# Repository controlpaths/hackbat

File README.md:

# Hackbat

HackBat is an open-source device designed for hackers and makers to experiment with different pen-testing techniques. The device is based on the Raspberry Pi RP2040 microcontroller and has an RF transceiver, NFC, WIFI, OLED display...

## RP2040

The Raspberry Pi [RP2040](https://www.raspberrypi.com/products/rp2040/specifications/) is the brain of the HackBat. The main features of this MCU are:

- Dual-core Arm Cortex-M0+ processor, flexible clock running up to 133 MHz 264kB on-chip SRAM
- 2 × UART 
- 2 × SPI controllers
- 2 × I2C controllers
- 16 × PWM channels
- 1 × USB 1.1 controller and PHY, with host and device support
- 8 × Programmable I/O (PIO) state machines for custom peripheral support
- Operating temperature -40°C to +85°C
- Drag-and-drop programming using mass storage over USB
- Low-power sleep and dormant modes
- Temperature sensor
- Accelerated integer and floating-point libraries on-chip

The RP2040 can be programmed using Arduino IDE, Python or C++.

## Display

The OLED display used in the HackBat is a 128x64 pixels, with the driver SH110X. The device also allows OLED with SSD1306, but notice that the VCC and GND pins are reversed, so you need to change the 0 ohm resistors of those pins.

## RF

The Hackbat features a [CC1101](https://www.ti.com/product/CC1101) from Texas instruments. CC1101 is a low-cost sub-1 GHz transceiver designed for very low-power wireless applications. The circuit is mainly intended for the ISM (Industrial, scientific and Medical) and SRD (Short Range Device) frequency bands at 315, 433, 868, and 915 MHz, but can easily be programmed for operation at other frequencies in the 300-348 MHz, 387-464 MHz and 779-928 MHz bands

## WIFI

The hackBat features an ESP8266 module, the ESP-12F. This module allow either the HackBat to connect a WIFI network, or generate an access point to allow connections.

The ESP-12F modules can be programmed using the Arduino IDE and the UART conenction. In the HackBat, the ESP-12F is programmed through the RP2040 by using it as USB-UART bridge.

## NFC

HackBat has NFC communication at 13.56MHz. The IC in charge of this peripheral is the [PN532].

PN532 is a highly integrated transceiver module for contactless communication at 13.56 MHz based on the 80C51 microcontroller core supporting different card and reader/writer operating modes.

HackBat uses [this](https://es.aliexpress.com/item/1005006005040320.html?spm=a2g0o.productlist.main.13.65b05927VOBhfq&algo_pvid=9ccfed98-181b-4e28-b2be-488f5ec17187&algo_exp_id=9ccfed98-181b-4e28-b2be-488f5ec17187-6&pdp_npi=4%40dis%21EUR%218.71%210.99%21%21%2166.15%217.50%21%402103854017142998536557342eb34a%2112000035367480068%21sea%21ES%210%21AB&curPageLogUid=pD9zsZTxZuDe&utparam-url=scene%3Asearch%7Cquery_from%3A) integrated module with the PN532.

The communication with the RP2040 is I2C.

## Keyboard emulation

Since the RP2040 has USB host/Device, the HackBat can be used as a keyboard emulator using the Arduinoi `keyboard.h` library.

## Get Yours

The HackBat is open-source, so you can use the output files to manufacture your own in [JLCPCB](https://jlcpcb.com/?from=controlpath). You just need to compress the `output_files` directory, and upload it to [JLCPCB](https://jlcpcb.com/?from=controlpath). 

Remember to change the Surface Finish to **LeadFree HASL** to make your board ROHS compliant.

Then you have to add the PCB Assembly service and upload the [centroid](./kicad/hackbat/production_files/hackbat-all-pos.csv) file, and the [BOM](./kicad/hackbat/production_files/bom.csv). 

In a few days, you will receive your board at home.

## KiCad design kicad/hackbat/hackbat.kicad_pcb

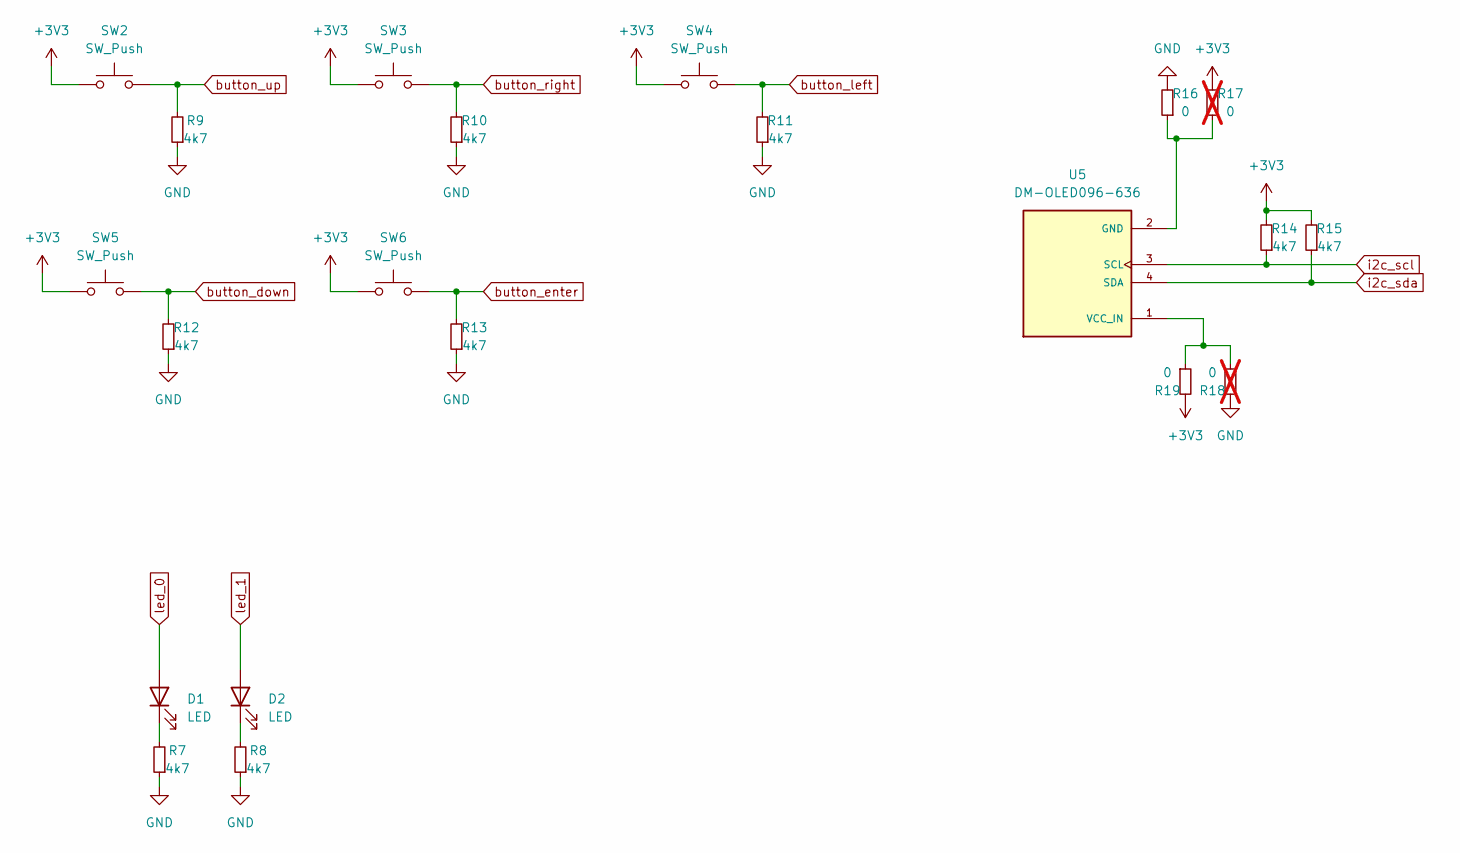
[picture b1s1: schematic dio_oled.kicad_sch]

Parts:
D1, D2: LED; LED_0603_1608Metric
R7, R8, R9, R10, R11, R12, R13, R14, R15: 4k7; R_0603_1608Metric
R16, R19: 0; R_0603_1608Metric
R17, R18: 0; R_0603_1608Metric; not fitted
SW2, SW3, SW4, SW5, SW6: SW_Push; SW_Push_1P1T_NO_6x6mm_H9.5mm; JLCPCB Part # C455109
U5: DM-OLED096-636; oled_1.3; PARTREV 2018-09-10

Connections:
+3V3: R14.2, R15.2, R17.2, R19.2, SW2.1, SW3.1, SW4.1, SW5.1, SW6.1; also elsewhere on the board
GND: R7.1, R8.1, R9.1, R10.1, R11.1, R12.1, R13.1, R16.2, R18.2; also elsewhere on the board
unnamed: D1.1 (K), R7.2
unnamed: D2.1 (K), R8.2
unnamed: R16.1, R17.1, U5.2 (GND)
unnamed: R18.1, R19.1, U5.1 (VCC_IN)
button_down: R12.2, SW5.2; also elsewhere on the board
button_enter: R13.2, SW6.2; also elsewhere on the board
button_left: R11.2, SW4.2; also elsewhere on the board
button_right: R10.2, SW3.2; also elsewhere on the board
button_up: R9.2, SW2.2; also elsewhere on the board
i2c_scl: R14.1, U5.3 (SCL); also elsewhere on the board
i2c_sda: R15.1, U5.4 (SDA); also elsewhere on the board
led_0: D1.2 (A); also elsewhere on the board
led_1: D2.2 (A); also elsewhere on the board

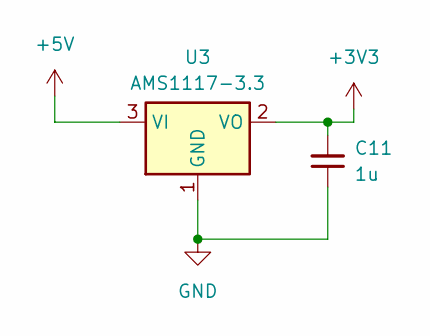
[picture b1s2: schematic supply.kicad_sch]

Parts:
C11: 1u; C_0603_1608Metric
U3: AMS1117-3.3; SOT-223-3_TabPin2

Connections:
+3V3: C11.2, U3.2 (VO); also elsewhere on the board
+5V: U3.3 (VI); also elsewhere on the board
GND: C11.1, U3.1 (GND); also elsewhere on the board

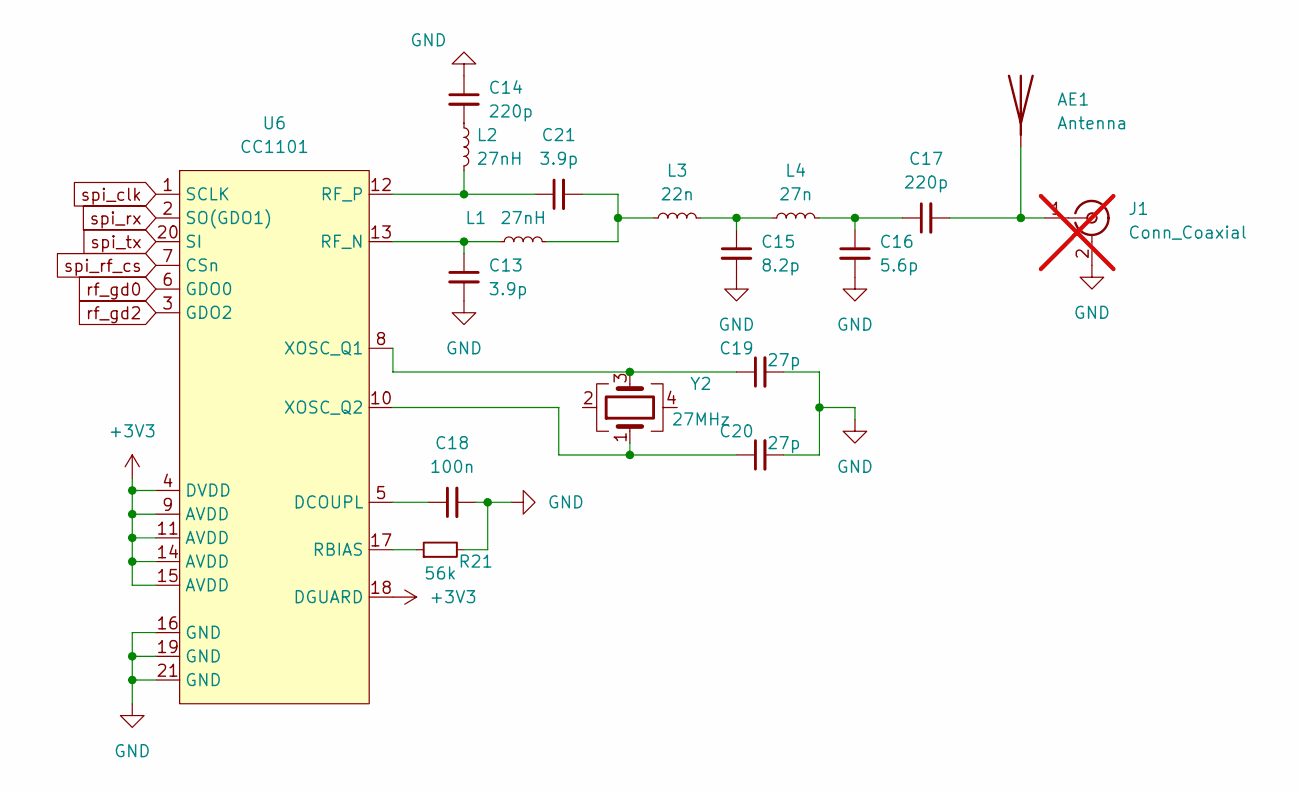
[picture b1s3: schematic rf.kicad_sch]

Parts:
AE1: Antenna; TestPoint_THTPad_1.5x1.5mm_Drill0.7mm
C13, C21: 3.9p; C_0402_1005Metric
C14, C17: 220p; C_0402_1005Metric
C15: 8.2p; C_0402_1005Metric
C16: 5.6p; C_0402_1005Metric
C18: 100n; C_0402_1005Metric
C19, C20: 27p; C_0402_1005Metric
J1: Conn_Coaxial; SMA_Amphenol_132289_EdgeMount; not fitted
L1, L2: 27nH; L_0402_1005Metric
L3: 22n; L_0402_1005Metric
L4: 27n; L_0402_1005Metric
R21: 56k; R_0402_1005Metric
U6: CC1101; QFN-20-1EP_4x4mm_P0.5mm_EP2.6x2.6mm_ThermalVias; JLCPCB Part # C29953
Y2: 27MHz; Crystal_SMD_3225-4Pin_3.2x2.5mm; JLCPCB Part # C254353

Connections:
+3V3: U6.4 (DVDD), U6.9 (AVDD), U6.11 (AVDD), U6.14 (AVDD), U6.15 (AVDD), U6.18 (DGUARD); also elsewhere on the board
GND: C13.2, C14.1, C15.2, C16.2, C18.2, C19.2, C20.2, J1.2 (Ext), R21.2, U6.16 (GND), U6.19 (GND), U6.21 (GND); also elsewhere on the board
unnamed: AE1.1 (A), C17.2, J1.1 (In)
unnamed: C14.2, L2.1
unnamed: C15.1, L3.2, L4.1
unnamed: C16.1, C17.1, L4.2
unnamed: C21.2, L1.2, L3.1
unnamed: C18.1, U6.5 (DCOUPL)
unnamed: R21.1, U6.17 (RBIAS)
unnamed: C13.1, L1.1, U6.13 (RF_N)
unnamed: C21.1, L2.2, U6.12 (RF_P)
unnamed: C19.1, U6.8 (XOSC_Q1), Y2.3
unnamed: C20.1, U6.10 (XOSC_Q2), Y2.1
rf_gd0: U6.6 (GDO0); also elsewhere on the board
rf_gd2: U6.3 (GDO2); also elsewhere on the board
spi_clk: U6.1 (SCLK); also elsewhere on the board
spi_rf_cs: U6.7 (CSn); also elsewhere on the board
spi_rx: U6.2 (SO(GDO1)); also elsewhere on the board
spi_tx: U6.20 (SI); also elsewhere on the board

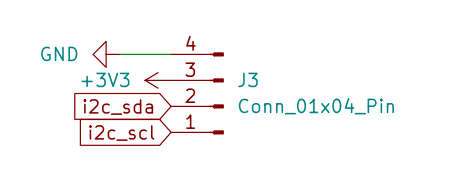
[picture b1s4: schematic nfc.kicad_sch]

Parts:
J3: Conn_01x04_Pin; PinHeader_1x04_P2.54mm_Vertical

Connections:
+3V3: J3.3; also elsewhere on the board
GND: J3.4; also elsewhere on the board
i2c_scl: J3.1; also elsewhere on the board
i2c_sda: J3.2; also elsewhere on the board

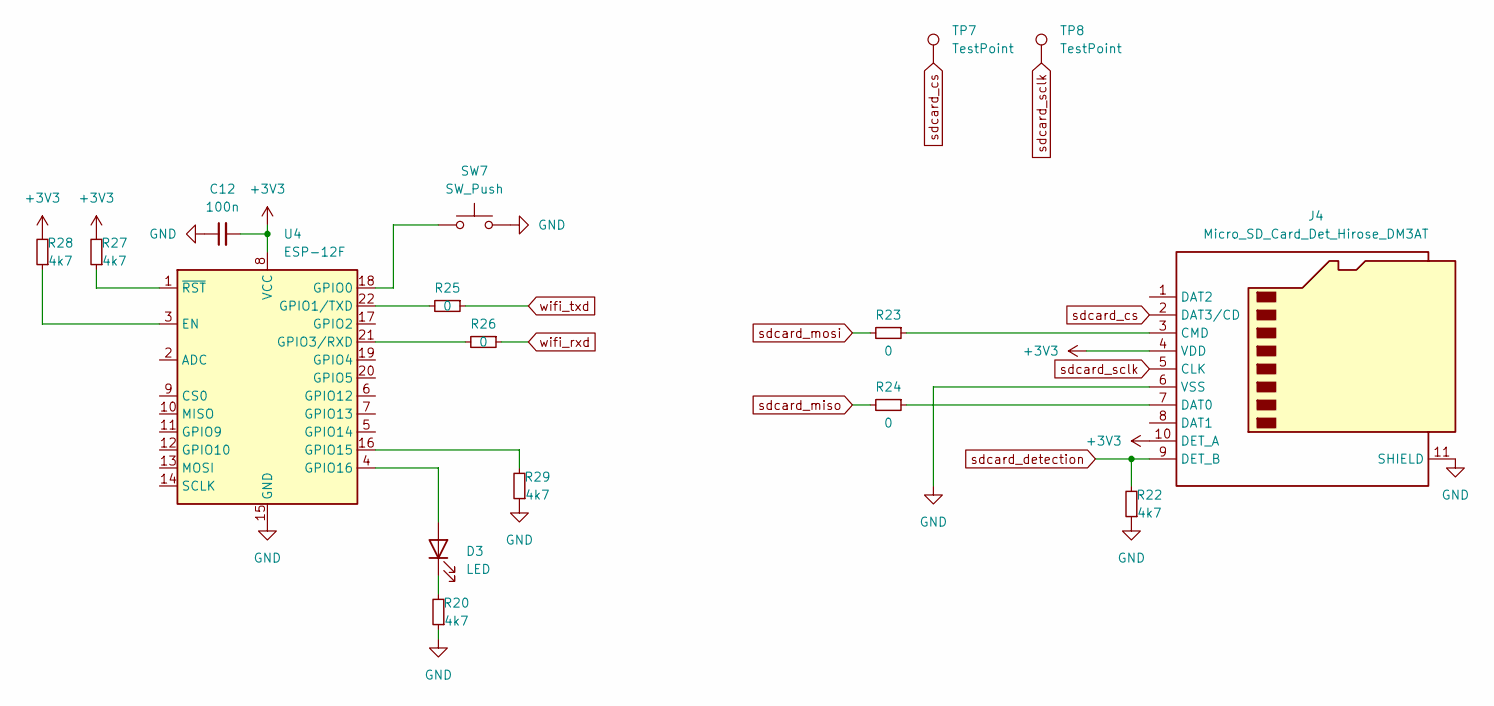
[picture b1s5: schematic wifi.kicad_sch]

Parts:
C12: 100n; C_0603_1608Metric
D3: LED; LED_0603_1608Metric
J4: Micro_SD_Card_Det_Hirose_DM3AT; microSD_HC_Hirose_DM3AT-SF-PEJM5; JLCPCB Part # C114218
R20, R22, R27, R28, R29: 4k7; R_0603_1608Metric
R23, R24, R25, R26: 0; R_0603_1608Metric
SW7: SW_Push; SW_Push_SPST_NO_Alps_SKRK; JLCPCB Part # C115357
TP7, TP8: TestPoint; TestPoint_Pad_D1.0mm
U4: ESP-12F; ESP-12E; JLCPCB Part # C784365

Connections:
+3V3: C12.2, J4.4 (VDD), J4.10 (DET_A), R27.2, R28.2, U4.8 (VCC); also elsewhere on the board
GND: C12.1, J4.6 (VSS), J4.11 (SHIELD), R20.1, R22.1, R29.1, SW7.2, U4.15 (GND); also elsewhere on the board
unnamed: D3.2 (A), U4.4 (GPIO16)
unnamed: D3.1 (K), R20.2
unnamed: J4.3 (CMD), R23.1
unnamed: J4.7 (DAT0), R24.1
unnamed: R28.1, U4.3 (EN)
unnamed: SW7.1, U4.18 (GPIO0)
unnamed: R25.2, U4.22 (GPIO1/TXD)
unnamed: R26.2, U4.21 (GPIO3/RXD)
unnamed: R29.2, U4.16 (GPIO15)
unnamed: R27.1, U4.1 (~RST)
sdcard_cs: J4.2 (DAT3/CD), TP7.1; also elsewhere on the board
sdcard_detection: J4.9 (DET_B), R22.2; also elsewhere on the board
sdcard_miso: R24.2; also elsewhere on the board
sdcard_mosi: R23.2; also elsewhere on the board
sdcard_sclk: J4.5 (CLK), TP8.1; also elsewhere on the board
wifi_rxd: R26.1; also elsewhere on the board
wifi_txd: R25.1; also elsewhere on the board

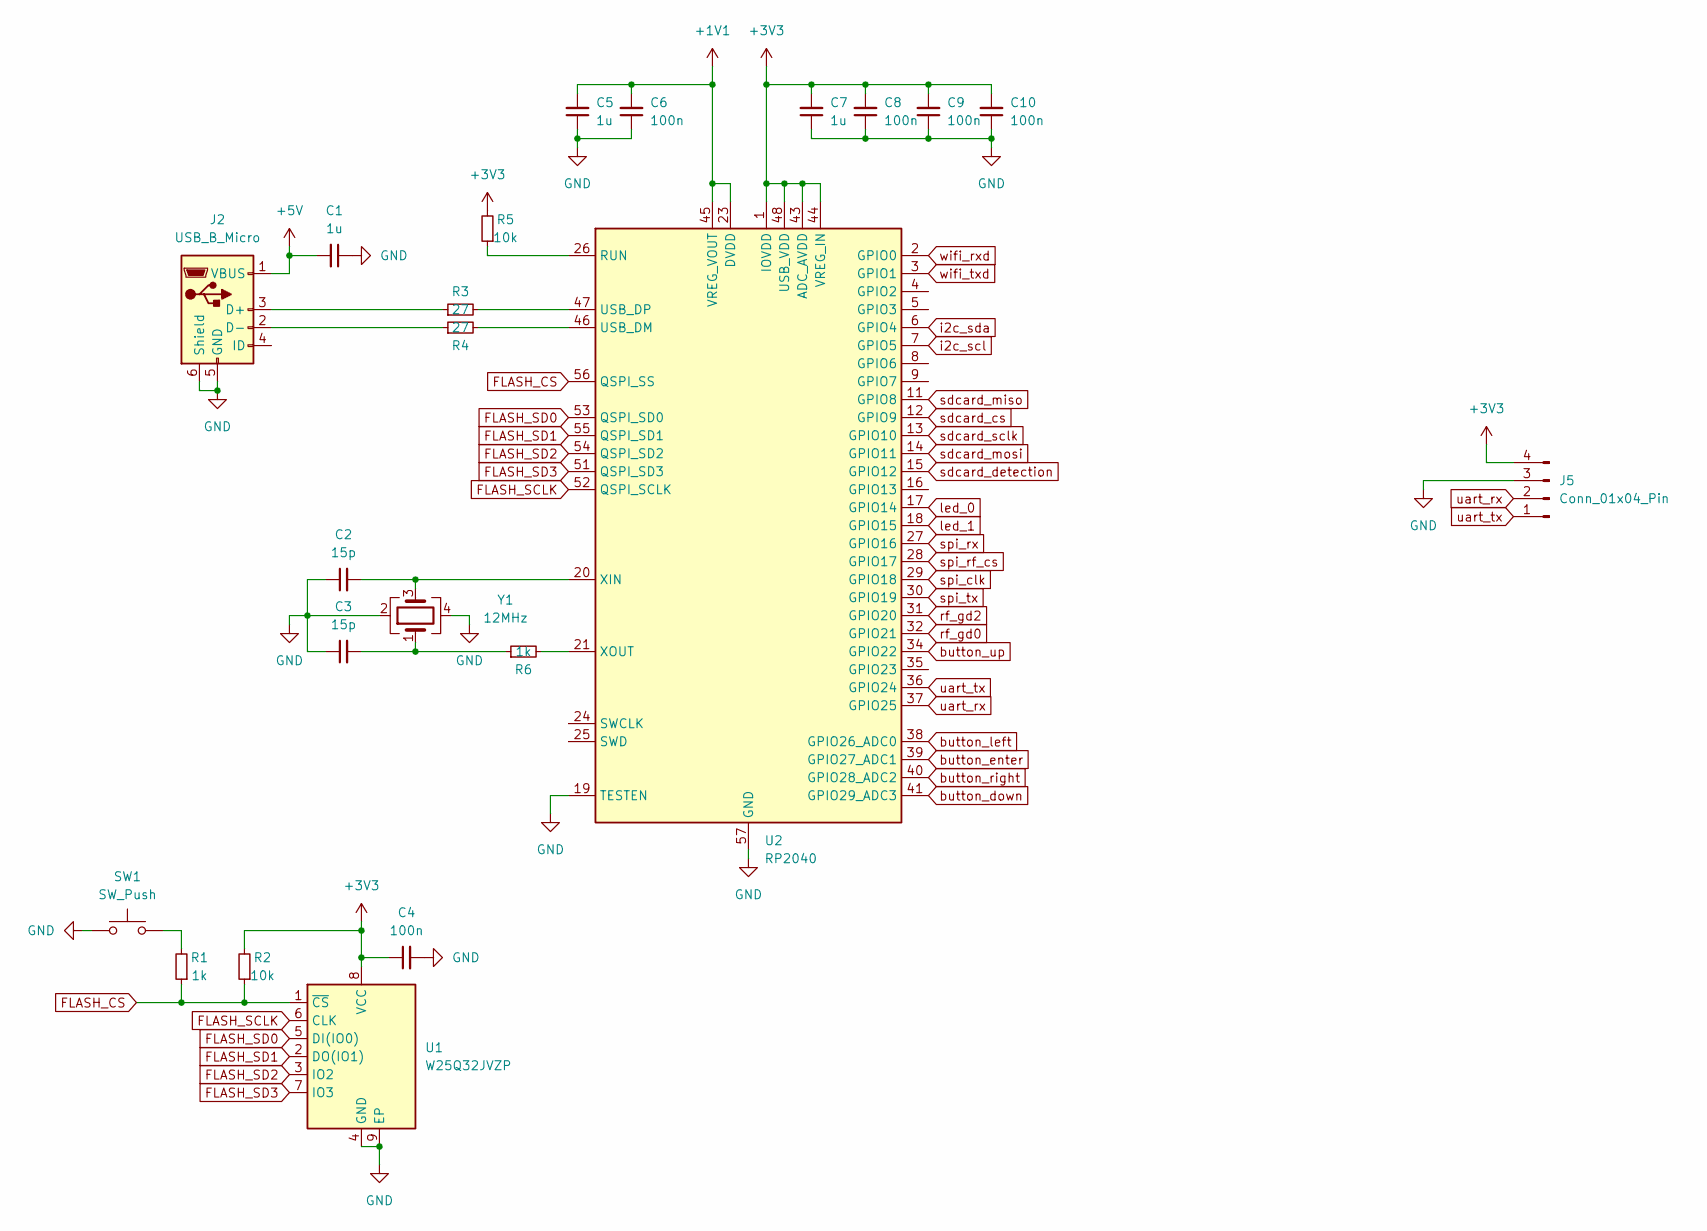
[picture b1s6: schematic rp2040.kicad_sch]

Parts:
C1, C5, C7: 1u; C_0603_1608Metric
C2, C3: 15p; C_0603_1608Metric
C4, C6, C8, C9, C10: 100n; C_0603_1608Metric
J2: USB_B_Micro; USB_Micro-B_Amphenol_10118193-0001LF_Horizontal; JLCPCB Part # C132562
J5: Conn_01x04_Pin; PinHeader_1x04_P2.54mm_Horizontal
R1, R6: 1k; R_0603_1608Metric
R2, R5: 10k; R_0603_1608Metric
R3, R4: 27; R_0603_1608Metric
SW1: SW_Push; SW_Push_SPST_NO_Alps_SKRK; JLCPCB Part # C115357
U1: W25Q32JVZP; WSON-8-1EP_6x5mm_P1.27mm_EP3.4x4.3mm; JLCPCB Part # C2940197
U2: RP2040; QFN-56-1EP_7x7mm_P0.4mm_EP3.2x3.2mm; JLCPCB Part # C2040
Y1: 12MHz; Crystal_SMD_3225-4Pin_3.2x2.5mm; JLCPCB Part # C524716

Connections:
+1V1: C5.2, C6.2, U2.23 (DVDD), U2.45 (VREG_VOUT), U2.50 (DVDD)
+3V3: C4.1, C7.2, C8.2, C9.2, C10.2, J5.4, R2.2, R5.2, U1.8 (VCC), U2.1 (IOVDD), U2.10 (IOVDD), U2.22 (IOVDD), U2.33 (IOVDD), U2.42 (IOVDD), U2.43 (ADC_AVDD), U2.44 (VREG_IN), U2.48 (USB_VDD), U2.49 (IOVDD); also elsewhere on the board
+5V: C1.2, J2.1 (VBUS); also elsewhere on the board
FLASH_CS: R1.1, R2.1, U1.1 (~CS), U2.56 (QSPI_SS)
FLASH_SCLK: U1.6 (CLK), U2.52 (QSPI_SCLK)
FLASH_SD0: U1.5 (DI(IO0)), U2.53 (QSPI_SD0)
FLASH_SD1: U1.2 (DO(IO1)), U2.55 (QSPI_SD1)
FLASH_SD2: U1.3 (IO2), U2.54 (QSPI_SD2)
FLASH_SD3: U1.7 (IO3), U2.51 (QSPI_SD3)
GND: C1.1, C2.1, C3.1, C4.2, C5.1, C6.1, C7.1, C8.1, C9.1, C10.1, J2.5 (GND), J2.6 (Shield), J5.3, SW1.1, U1.4 (GND), U1.9 (EP), U2.19 (TESTEN), U2.57 (GND), Y1.2, Y1.4; also elsewhere on the board
unnamed: C3.2, R6.1, Y1.1
unnamed: J2.3 (D+), R3.1
unnamed: J2.2 (D-), R4.1
unnamed: R1.2, SW1.2
unnamed: R5.1, U2.26 (RUN)
unnamed: R4.2, U2.46 (USB_DM)
unnamed: R3.2, U2.47 (USB_DP)
unnamed: C2.2, U2.20 (XIN), Y1.3
unnamed: R6.2, U2.21 (XOUT)
button_down: U2.41 (GPIO29_ADC3); also elsewhere on the board
button_enter: U2.39 (GPIO27_ADC1); also elsewhere on the board
button_left: U2.38 (GPIO26_ADC0); also elsewhere on the board
button_right: U2.40 (GPIO28_ADC2); also elsewhere on the board
button_up: U2.34 (GPIO22); also elsewhere on the board
i2c_scl: U2.7 (GPIO5); also elsewhere on the board
i2c_sda: U2.6 (GPIO4); also elsewhere on the board
led_0: U2.17 (GPIO14); also elsewhere on the board
led_1: U2.18 (GPIO15); also elsewhere on the board
rf_gd0: U2.32 (GPIO21); also elsewhere on the board
rf_gd2: U2.31 (GPIO20); also elsewhere on the board
sdcard_cs: U2.12 (GPIO9); also elsewhere on the board
sdcard_detection: U2.15 (GPIO12); also elsewhere on the board
sdcard_miso: U2.11 (GPIO8); also elsewhere on the board
sdcard_mosi: U2.14 (GPIO11); also elsewhere on the board
sdcard_sclk: U2.13 (GPIO10); also elsewhere on the board
spi_clk: U2.29 (GPIO18); also elsewhere on the board
spi_rf_cs: U2.28 (GPIO17); also elsewhere on the board
spi_rx: U2.27 (GPIO16); also elsewhere on the board
spi_tx: U2.30 (GPIO19); also elsewhere on the board
uart_rx: J5.2, U2.37 (GPIO25)
uart_tx: J5.1, U2.36 (GPIO24)
wifi_rxd: U2.2 (GPIO0); also elsewhere on the board
wifi_txd: U2.3 (GPIO1); also elsewhere on the board

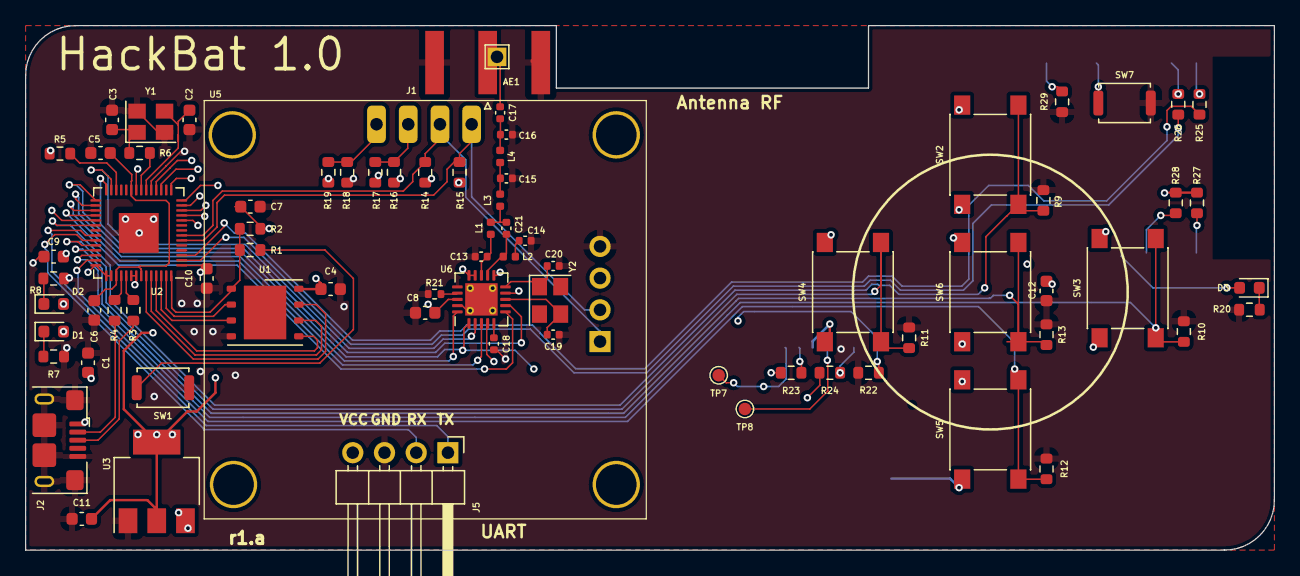
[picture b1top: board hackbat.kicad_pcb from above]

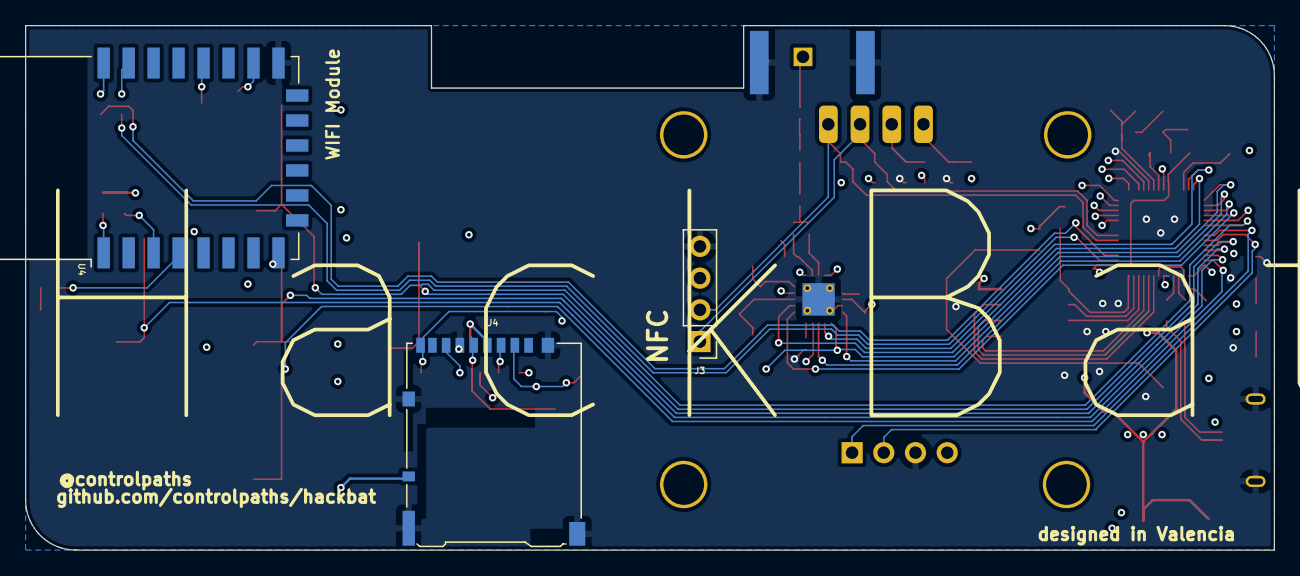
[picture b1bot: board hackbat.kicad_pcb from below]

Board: 4 copper layers, 100.0 x 42.0 mm, 80 parts (3 on the bottom side), 68 nets.

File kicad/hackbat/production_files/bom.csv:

#,Reference,Qty,Value,Footprint,DNP,JLCPCB Part #
1,AE1,1,Antenna,TestPoint:TestPoint_THTPad_1.5x1.5mm_Drill0.7mm,,
2,"C1, C5, C7, C11",4,1u,Capacitor_SMD:C_0603_1608Metric,,
3,"C2, C3",2,15p,Capacitor_SMD:C_0603_1608Metric,,
4,"C4, C6, C8, C9, C10, C12",6,100n,Capacitor_SMD:C_0603_1608Metric,,
5,"C13, C21",2,3.9p,Capacitor_SMD:C_0402_1005Metric,,
6,"C14, C17",2,220p,Capacitor_SMD:C_0402_1005Metric,,
7,C15,1,8.2p,Capacitor_SMD:C_0402_1005Metric,,
8,C16,1,5.6p,Capacitor_SMD:C_0402_1005Metric,,
9,C18,1,100n,Capacitor_SMD:C_0402_1005Metric,,
10,"C19, C20",2,27p,Capacitor_SMD:C_0402_1005Metric,,
11,"D1, D2, D3",3,LED,LED_SMD:LED_0603_1608Metric,,C19189746
13,J2,1,USB_B_Micro,Connector_USB:USB_Micro-B_Amphenol_10118193-0001LF_Horizontal,,C132562
15,J4,1,Micro_SD_Card_Det_Hirose_DM3AT,Connector_Card:microSD_HC_Hirose_DM3AT-SF-PEJM5,,C114218
16,J5,1,Conn_01x04_Pin,Connector_PinHeader_2.54mm:PinHeader_1x04_P2.54mm_Horizontal,,
17,"L1, L2",2,27nH,Inductor_SMD:L_0402_1005Metric,,
18,L3,1,22n,Inductor_SMD:L_0402_1005Metric,,
19,L4,1,27n,Inductor_SMD:L_0402_1005Metric,,
20,"R1, R6",2,1k,Resistor_SMD:R_0603_1608Metric,,
21,"R2, R5",2,10k,Resistor_SMD:R_0603_1608Metric,,
22,"R3, R4",2,27,Resistor_SMD:R_0603_1608Metric,,
23,"R7, R8, R9, R10, R11, R12, R13, R14, R15, R20, R22, R27, R28, R29",14,4k7,Resistor_SMD:R_0603_1608Metric,,
24,"R16, R19, R23, R24, R25, R26",6,0,Resistor_SMD:R_0603_1608Metric,,
26,R21,1,56k,Resistor_SMD:R_0402_1005Metric,,
27,"SW1, SW7",2,SW_Push,Button_Switch_SMD:SW_Push_SPST_NO_Alps_SKRK,,C115357
28,"SW2, SW3, SW4, SW5, SW6",5,SW_Push,Button_Switch_SMD:SW_Push_1P1T_NO_6x6mm_H9.5mm,,C455109
30,U1,1,W25Q32JVZP,Package_SON:WSON-8-1EP_6x5mm_P1.27mm_EP3.4x4.3mm,,C2940197
31,U2,1,RP2040,Package_DFN_QFN:QFN-56-1EP_7x7mm_P0.4mm_EP3.2x3.2mm,,C2040
32,U3,1,AMS1117-3.3,Package_TO_SOT_SMD:SOT-223-3_TabPin2,,
33,U4,1,ESP-12F,RF_Module:ESP-12E,,C784365
35,U6,1,CC1101,Package_DFN_QFN:QFN-20-1EP_4x4mm_P0.5mm_EP2.6x2.6mm_ThermalVias,,C29953
36,Y1,1,12MHz,Crystal:Crystal_SMD_3225-4Pin_3.2x2.5mm,,C524716
37,Y2,1,27MHz,Crystal:Crystal_SMD_3225-4Pin_3.2x2.5mm,,C254353

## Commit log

2024-05-01 HW complete. Production files ready.
2024-05-16 docs: update README.md
    cientific -> scientific
2024-06-11 Create LICENSE
